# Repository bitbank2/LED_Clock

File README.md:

# LED_Clock
A CH32V003 low cost 'night clock'<br>
The PCB project was created with KiCad 7.0 and the firmware in the MounRiver Studio IDE. The target device is the TSSOP20 version of the CH32V003.
<br>

<br>
<b>Why did you make it?</b><br>
We like to sleep in a completely black room with no LEDs visible. In the winter, the sun comes up later in the morning and it's useful to know what time it is if you wake up too early and can try to sleep a bit more. My idea was to create an LED clock which displays the time in the day and goes completely black at night. To display the time in a dark room, you wave your hand close to the clock and it will dimly display the time for a few seconds.<br>
<br>
The KiCad project files and gerbers (ready to produce at your favorite PCB fab) are in the PCB folder.<br>

If you find this project useful, please consider becoming a sponsor or sending a donation.

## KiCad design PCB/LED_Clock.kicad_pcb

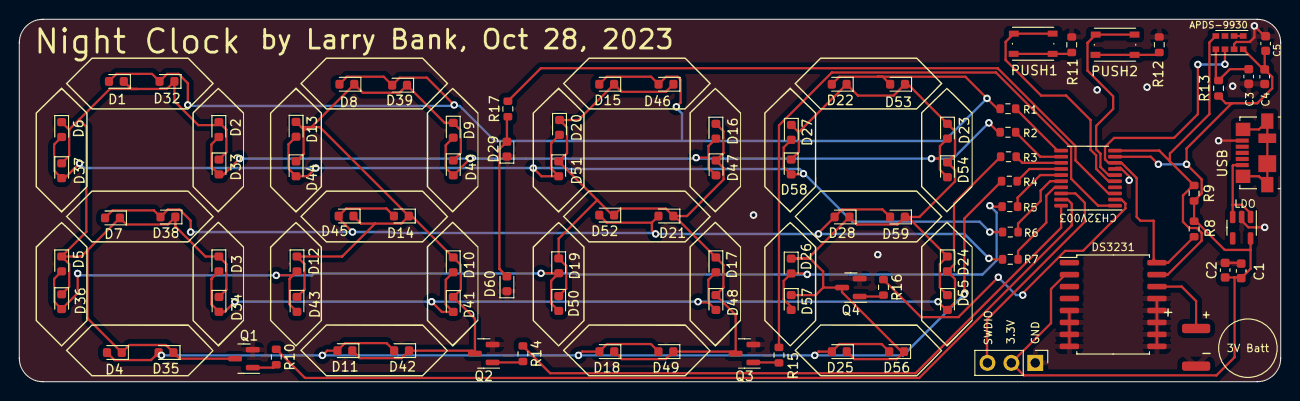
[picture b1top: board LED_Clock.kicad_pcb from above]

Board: 2 copper layers, 134.0 x 38.5 mm, 93 parts (0 on the bottom side), 41 nets.

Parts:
3V Batt: Battery_Cell; CR44_Tabs
APDS-9930: APDS-9960; Avago_APDS-9960
C1, C5: 10uF; C_0603_1608Metric
C2: 100n; C_0603_1608Metric
C3, C4: 1uF; C_0603_1608Metric
CH32V003: CH32V003_TSSOP20; TSSOP-20_4.4x6.5mm_P0.65mm
D1, D2, D3, D4, D5, D6, D7, D8, D9, D10, D11, D12, D13, D14, D15, D16, D17, D18, D19, D20, D21, D22, D23, D24, D25, D26, D27, D28, D29, D32, D33, D34, D35, D36, D37, D38, D39, D40, D41, D42, D43, D44, D45, D46, D47, D48, D49, D50, D51, D52, D53, D54, D55, D56, D57, D58, D59, D60: LED; LED_0603_1608Metric
DS3231: DS3231M; SOIC-16W_7.5x10.3mm_P1.27mm
J3: PROG; PinHeader_1x03_P2.54mm_Vertical
LDO: AP2127K-3.3; SOT-23-5
PUSH1, PUSH2: SW_Push; SW_Push_1P1T_NO_Vertical_Wuerth_434133025816
Q1, Q2, Q3, Q4: AO3400A; SOT-23
R1, R2, R3, R4, R5, R6, R7, R17: 1K; R_0603_1608Metric
R8, R9: 4.7K; R_0603_1608Metric
R10, R14, R15, R16: 1k; R_0603_1608Metric
R11, R12: 10K; R_0603_1608Metric
R13: 22R; R_0603_1608Metric
USB: USB_B_Micro; USB_Micro-B_Molex_47346-0001

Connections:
+3.3V: APDS-9930.5 (LED_A), C1.1, C2.1, C4.1, C5.1, CH32V003.9 (VDD), DS3231.2 (VCC), J3.2, LDO.5 (VOUT), R8.2, R9.2, R13.2
BUTT0: CH32V003.5 (PA1/OSCI), PUSH1.2
BUTT1: CH32V003.6 (PA2/OSCO), PUSH2.2
COL1: CH32V003.19 (PD2), R10.1
COL2: CH32V003.20 (PD3), R14.1
COL3: CH32V003.1 (PD4), R15.1
COL4: CH32V003.2 (PD5), R16.1
COLON: CH32V003.3 (PD6), R17.2
GND: 3V Batt.2 (-), APDS-9930.6 (GND), C1.2, C2.2, C3.2, C4.2, C5.2, CH32V003.7 (VSS), D29.1 (K), D60.1 (K), DS3231.5 (GND), DS3231.6 (GND), DS3231.7 (GND), DS3231.8 (GND), DS3231.9 (GND), DS3231.10 (GND), DS3231.11 (GND), DS3231.12 (GND), DS3231.13 (GND), J3.1, LDO.2 (GND), Q1.2 (S), Q2.2 (S), Q3.2 (S), Q4.2 (S), R11.2, R12.2, USB.5 (GND)
unnamed: D1.2 (A), D8.2 (A), D15.2 (A), D22.2 (A), D32.2 (A), D39.2 (A), D46.2 (A), D53.2 (A), R1.1
unnamed: D1.1 (K), D2.1 (K), D3.1 (K), D4.1 (K), D5.1 (K), D6.1 (K), D7.1 (K), D32.1 (K), D33.1 (K), D34.1 (K), D35.1 (K), D36.1 (K), D37.1 (K), D38.1 (K), Q1.3 (D)
unnamed: D3.2 (A), D10.2 (A), D17.2 (A), D24.2 (A), D34.2 (A), D41.2 (A), D48.2 (A), D55.2 (A), R3.1
unnamed: D8.1 (K), D9.1 (K), D10.1 (K), D11.1 (K), D12.1 (K), D13.1 (K), D14.1 (K), D39.1 (K), D40.1 (K), D41.1 (K), D42.1 (K), D43.1 (K), D44.1 (K), D45.1 (K), Q2.3 (D)
unnamed: D4.2 (A), D11.2 (A), D18.2 (A), D25.2 (A), D35.2 (A), D42.2 (A), D49.2 (A), D56.2 (A), R4.1
unnamed: D5.2 (A), D12.2 (A), D19.2 (A), D26.2 (A), D36.2 (A), D43.2 (A), D50.2 (A), D57.2 (A), R5.1
unnamed: D6.2 (A), D13.2 (A), D20.2 (A), D27.2 (A), D37.2 (A), D44.2 (A), D51.2 (A), D58.2 (A), R6.1
unnamed: D7.2 (A), D14.2 (A), D21.2 (A), D28.2 (A), D38.2 (A), D45.2 (A), D52.2 (A), D59.2 (A), R7.1
unnamed: D15.1 (K), D16.1 (K), D17.1 (K), D18.1 (K), D19.1 (K), D20.1 (K), D21.1 (K), D46.1 (K), D47.1 (K), D48.1 (K), D49.1 (K), D50.1 (K), D51.1 (K), D52.1 (K), Q3.3 (D)
unnamed: D2.2 (A), D9.2 (A), D16.2 (A), D23.2 (A), D33.2 (A), D40.2 (A), D47.2 (A), D54.2 (A), R2.1
unnamed: D22.1 (K), D23.1 (K), D24.1 (K), D25.1 (K), D26.1 (K), D27.1 (K), D28.1 (K), D53.1 (K), D54.1 (K), D55.1 (K), D56.1 (K), D57.1 (K), D58.1 (K), D59.1 (K), Q4.3 (D)
unnamed: D29.2 (A), D60.2 (A), R17.1
unnamed: PUSH1.1, R11.1
unnamed: PUSH2.1, R12.1
unnamed: Q1.1 (G), R10.2
unnamed: Q2.1 (G), R14.2
unnamed: Q3.1 (G), R15.2
unnamed: Q4.1 (G), R16.2
unnamed: APDS-9930.3 (LDR), APDS-9930.4 (LED_K)
unnamed: APDS-9930.8 (VCC), C3.1, R13.1
ROW1: CH32V003.11 (PC1/SDA1), R1.2
ROW2: CH32V003.12 (PC2/SCL1), R2.2
ROW3: CH32V003.13 (PC3), R3.2
ROW4: CH32V003.14 (PC4), R4.2
ROW5: CH32V003.15 (PC5), R5.2
ROW6: CH32V003.16 (PC6), R6.2
ROW7: CH32V003.17 (PC7), R7.2
SCL: APDS-9930.7 (SCL), CH32V003.8 (PD0/SDA0), DS3231.16 (SCL), R8.1
SDA: APDS-9930.1 (SDA), CH32V003.10 (PC0), DS3231.15 (SDA), R9.1
SWDIO: CH32V003.18 (PD1/SCL0), J3.3
VBAT: 3V Batt.1 (+), DS3231.14 (VBAT)
VBUS: LDO.1 (VIN), LDO.3 (EN), USB.1 (VBUS)

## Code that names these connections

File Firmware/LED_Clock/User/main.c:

//
// LED Clock
//
#include "debug.h"
#define CH32V003
#define BITBANG
#include "../../libraries/ch32v_hal.inl"
#include "../../libraries/rtc_eeprom.inl"
#include "../../libraries/bb_proximity.inl"

#define SDA_PIN 0xc0
#define SCL_PIN 0xd0
#define BUTT0_PIN 0xa1
#define BUTT1_PIN 0xa2
#define COLON_PIN 0xd6
struct tm myTime;
int iLux, iBrightness; // a value from 0 to 255 indicating PWM duty
#define MAX_BRIGHTNESS 256
uint8_t u8Cols[] = {0xd2, 0xd3, 0xd4, 0xd5, 0xd7};
const uint8_t u8Dig2Seg[10] = {0x3f<<1, 0x06<<1, 0x5b<<1, 0x4f<<1, 0x66<<1, 0x6d<<1, 0x7d<<1, 0x07<<1, 0x7f<<1, 0x6f<<1};

void Option_Byte_CFG(void)
{
    FLASH_Unlock();
    FLASH_EraseOptionBytes();
    FLASH_UserOptionByteConfig(OB_IWDG_SW, OB_STOP_NoRST, OB_STDBY_NoRST, OB_RST_NoEN);
    FLASH_Lock();
}

void ShowDigit(uint8_t u8Digit, uint8_t u8Column, int iBright, int iDelay)
{
	int iOn, iOff;
	uint8_t u8;

	if (iBright <= 0) {
		Delay_Us(iDelay);
		return;
	}
	iOn = (iDelay * iBright) >> 8;
	iOff = (iDelay - iOn);
	if (u8Column == 4) { // colon
		if (u8Digit) {
			digitalWrite(COLON_PIN, 1);
			Delay_Us(iOn);
			digitalWrite(COLON_PIN, 0);
			Delay_Us(iOff);
		} else {
			Delay_Us(iOn+iOff); // keep time consistent
		}
	} else {
		u8 = u8Dig2Seg[u8Digit];
		digitalWrite8(0xc0, u8);
		digitalWrite(u8Cols[u8Column], 1);
		Delay_Us(iOn);
		digitalWrite(u8Cols[u8Column], 0);
		Delay_Us(iOff);
	}
} /* ShowDigit() */

void AddMinutes(int iMin)
{
	myTime.tm_min += iMin;
	if (myTime.tm_min >= 60) {
		myTime.tm_min -= 60;
		myTime.tm_hour++;
		if (myTime.tm_hour > 23)
			myTime.tm_hour = 0;
	}
	rtcSetTime(&myTime);
} /* AddMinutes()*/

int GetDistance(void)
{
    int i, iLux, iDist;
    const uint8_t iDistLow[26] = {200,200,200,200,200,200,200,200,
                               200,200,150,140,130,120,110,105,
                               100,94,90,86,82,78,74,73,72,71};
    const uint8_t iDistHigh[26] = {  70, 68, 65, 60, 58, 55, 50, 48,
                                44, 42, 40, 38, 37, 36, 35, 34,
                                33, 32, 31, 30, 30, 30, 30, 30, 30, 30};
    i = bbp_getProximity();
    if (i < 192) iDist = iDistLow[i >> 3];
    else iDist = iDistHigh[(i >> 5)-6];
    return iDist;
} /* GetDistance() */

void UpdateBrightness(int iTicks)
{
    iLux = bbp_getLight();
    if (iLux <= 20 && iBrightness != 0 && iTicks == 0) { // room went dark
    	iBrightness = 0; // go dark
    } else if (iLux > 20 && iBrightness == 0) { // room went light
		iBrightness = 50+iLux;
		if (iBrightness > MAX_BRIGHTNESS) {
			iBrightness = MAX_BRIGHTNESS; // max brightness
		}
    }
} /* UpdateBrightness() */

int main(void)
{
int i, j, iTicks = 0;
int iDistance;
int iColor;

    NVIC_PriorityGroupConfig(NVIC_PriorityGroup_2);
    Delay_Init();
//    Option_Byte_CFG(); // allow PD7 to be used as GPIO
    rtcInit(RTC_DS3231, SDA_PIN, SCL_PIN);
    pinMode(BUTT0_PIN, INPUT_PULLUP);
    pinMode(BUTT1_PIN, INPUT_PULLUP);
    pinMode(COLON_PIN, OUTPUT);
    bbp_init();
    bbp_start(BBP_CAPS_ALS | BBP_CAPS_PROXIMITY);
    bbp_setLEDBoost(3);

    for (i=0; i<5; i++) {
    	pinMode(u8Cols[i], OUTPUT);
    	digitalWrite(u8Cols[i], 0);
    }
    for (i=0xc1; i<=0xc7; i++) { // enable all rows as outputs
    	pinMode(i, OUTPUT);
    	digitalWrite(i, 0);
    }
    rtcGetTime(&myTime);
    UpdateBrightness(0); // start from reset with the appropriate brightness
    while(1)
    {
 //   	i = bbp_getLight();
//    	i = bbp_getProximity();
        for (j=0; j<200; j++) {
#ifdef BOGUS
        	ShowDigit(i/1000, 0, iBrightness,1000);
        	ShowDigit((i % 1000)/100, 1, iBrightness, 1000);
        	ShowDigit((i % 100)/10, 2, iBrightness,1000);
        	ShowDigit(i % 10, 3, iBrightness, 1000);
#else
        	if (myTime.tm_hour > 9) {
        		i = myTime.tm_hour / 10;
   				ShowDigit(i, 0, iBrightness, 1000);
        	} else {
        		Delay_Us(1000);
        	}
        	i = myTime.tm_hour % 10;
   			ShowDigit(i, 1, iBrightness, 1000);
        	i = myTime.tm_min / 10;
   			ShowDigit(i, 2, iBrightness, 1000);
        	i = myTime.tm_min % 10;
   			ShowDigit(i, 3, iBrightness, 1000);
   			ShowDigit(myTime.tm_sec & 1, 4, iBrightness, 1000); // blinking colon
   			if ((j == 0 || j == 100) && digitalRead(BUTT1_PIN) == 0) { // fast change
   				AddMinutes(10);
   			}
#endif
        } // for j
		if (digitalRead(BUTT0_PIN) == 0) { // slow change
			AddMinutes(1);
		}

#ifndef FUTURE
		if ((myTime.tm_sec & 7) == 7) { // check light level every 8 seconds
			UpdateBrightness(iTicks);
		}
#endif
		if ((myTime.tm_sec & 15) == 15) {
	        rtcGetTime(&myTime); // keep the time accurate
		} else { // manually increment the time to prevent flicker on the LEDs
			myTime.tm_sec++;
			if (myTime.tm_sec >= 60) {
				myTime.tm_sec -= 60;
				myTime.tm_min++;
				if (myTime.tm_min >= 60) {
					myTime.tm_min -= 60;
					myTime.tm_hour++;
				}
			}
		}
#ifndef FUTURE
		if (iLux < 20) { // dark room
//			iDistance = GetDistance();
//			i = 160 - iDistance; // hand nearby?
		    i = bbp_getProximity();
			if (i > 2100)  { // hand nearby
				iTicks = 5;
				iBrightness = 20;
			} else if (iTicks > 0) {
				iTicks--;
				if (iTicks == 0) iBrightness = 0; // go black again after 5 seconds
			} else {
				Delay_Ms(250); // waiting for more samples
			}
		}
#endif
    }
} /* main() */

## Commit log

2023-10-28 added firmware
2023-12-07 Removed flicker and added APDS-9960 support
